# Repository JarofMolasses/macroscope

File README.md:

# Macroscope
This is a basic, constant-height, contact mode profilometer/AFM. It's really more of a demonstration piece but ~10 micron resolution can be achieved with some patience.

Inspired by this paper: [*Macro-scale atomic force microscope: An experimental platform for teaching precision mechatronics*](https://www.sciencedirect.com/science/article/abs/pii/S0957415815001488).

# Results
### Canadian nickel scanned at 1.75mm/s, 0.25mm resolution, 88x88 pixels 
A "quick" scan. It took 46 minutes.

### 3D printed test sample with 0.1mm steps. Scanned at 0.5mm/s, 0.05mm resolution, 60x20 pixels
You can see the diagonal print lines on the lowest step.

With a dollar for scale:

# Mechanical
## Initial working prototype 

## Second prototype 

# Control
This machine is programmed using SCPI-ish ASCII commands over a serial port.\
The control GUI we used for the prototype machines can be found here: https://github.com/JarofMolasses/macroscope_control. 

*Created by [David Antoniuk](https://github.com/DavidAntoniuk) and [myself](https://github.com/JarofMolasses).*

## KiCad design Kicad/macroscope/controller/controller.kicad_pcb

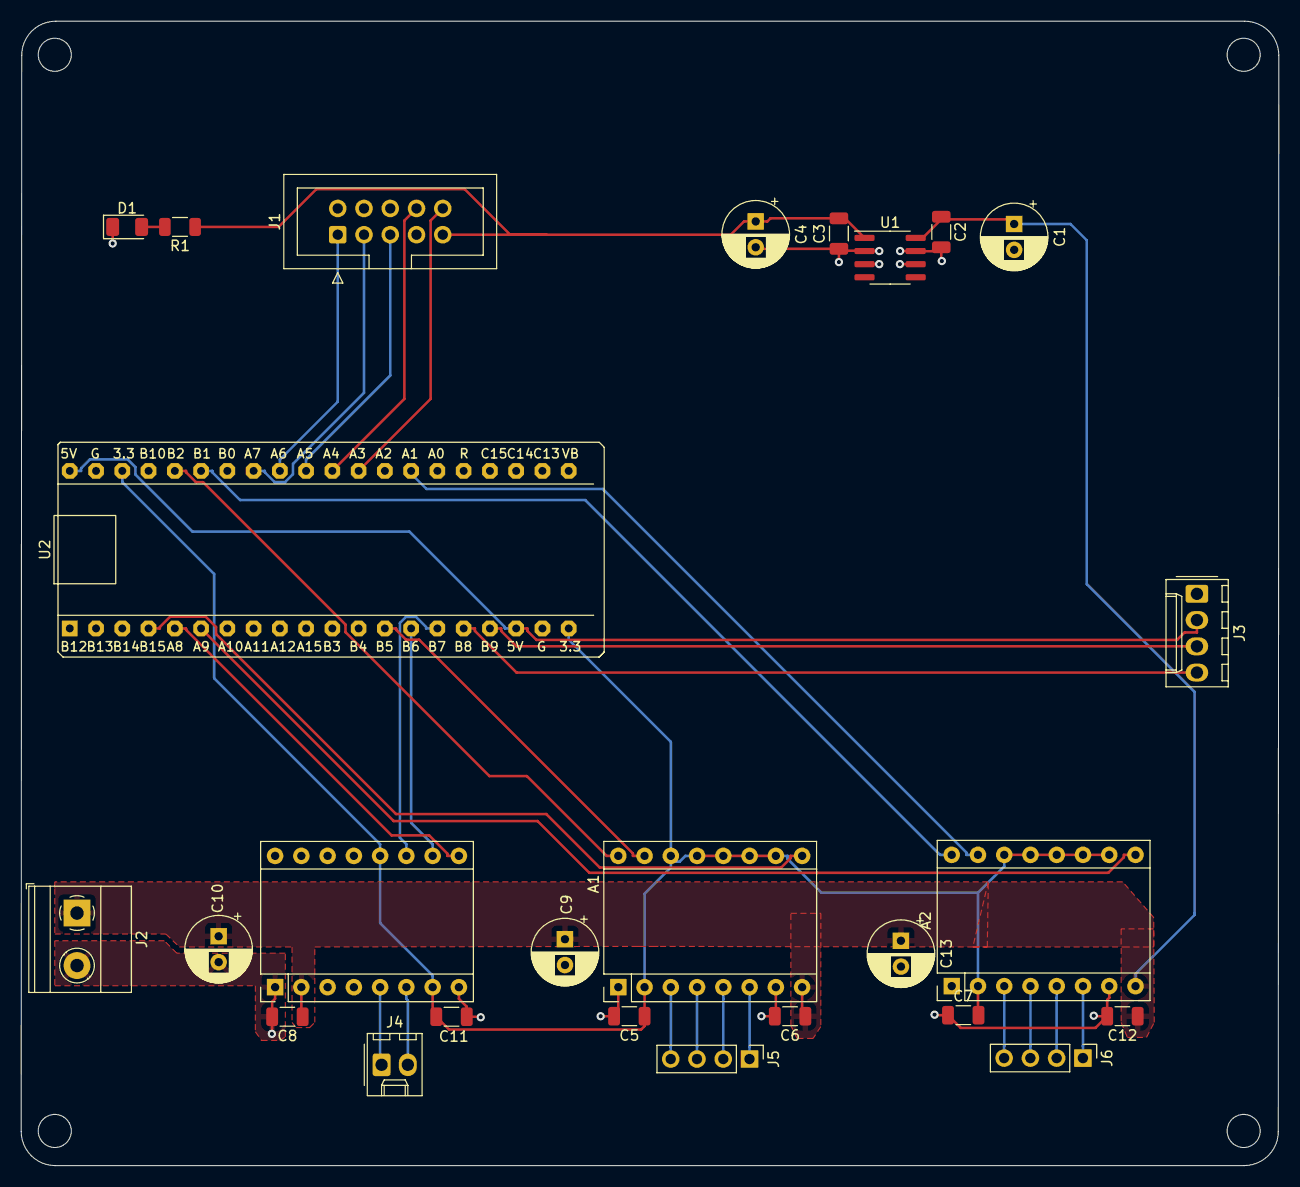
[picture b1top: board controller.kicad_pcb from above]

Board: 2 copper layers, 121.7 x 110.7 mm, 30 parts (0 on the bottom side), 32 nets.

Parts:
A1: A4988 Y axis driver; A4988_Pololu_Breakout-16_15.2x20.3mm
A2: A4988 X axis driver; A4988_Pololu_Breakout-16_15.2x20.3mm
C1, C4: 10u; CP_Radial_D6.3mm_P2.50mm
C2, C3, C6, C8, C12: 1u; C_1206_3216Metric
C5, C7, C11: 0.1u; C_1206_3216Metric
C9, C10, C13: 100u; CP_Radial_D6.3mm_P2.50mm
D1: LED; LED_1206_3216Metric
H1, H2, H3, H4: MountingHole; MountingHole_3.2mm_M3_ISO7380
J1: ADC board connector; IDC-Header_2x05_P2.54mm_Vertical
J2: 12V in; TerminalBlock_Phoenix_MKDS-1,5-2-5.08_1x02_P5.08mm_Horizont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
J3: I2C header; Molex_KK-254_AE-6410-04A_1x04_P2.54mm_Vertical
J4: Probe coil; Molex_KK-254_AE-6410-02A_1x02_P2.54mm_Vertical
J5: Y stepper; PinHeader_1x04_P2.54mm_Vertical
J6: X stepper; PinHeader_1x04_P2.54mm_Vertical
R1: 1k; R_1206_3216Metric
U1: LM78L05_SO8; SOIC-8_3.9x4.9mm_P1.27mm
U2: STM32F411 BlackPill; STM32F411_Black_Pill
U3: Coil driver; TB6612FNG_Pololu_Breakout-16_15.2x20.3mm

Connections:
+3V3: A1.2 (VDD), A1.10 (MS1), A1.11 (MS2), A1.12 (MS3), A1.13 (~RESET), A1.14 (~SLEEP), A2.2 (VDD), A2.10 (MS1), A2.11 (MS2), A2.12 (MS3), A2.13 (~RESET), A2.14 (~SLEEP), C5.1, C7.2, C11.1, U2.20 (3.3V), U2.38 (3.3V), U3.7 (VCC), U3.12 (STBY)
+5V: C3.1, C4.1, J1.9, R1.1, U1.1 (OUT)
+5VD: J3.2, U2.18 (5V), U2.40 (5V)
+12V: A1.8 (VMOT), A2.8 (VMOT), C1.1, C2.1, C6.1, C8.1, C9.1, C10.1, C12.1, C13.1, J2.1, U1.8 (IN), U3.2 (VMOT)
/Digital/COIL1: U2.14 (B6), U3.10 (AIN2)
/Digital/COIL2: U2.15 (B7), U3.11 (AIN1)
/Digital/DIRX: A1.16 (DIR), U2.36 (B2)
/Digital/DIRY: A2.16 (DIR), U2.35 (B1)
/Digital/ENX: A1.9 (~ENABLE), U2.4 (B15)
/Digital/ENY: A2.9 (~ENABLE), U2.6 (A9)
/Digital/PWM: U2.5 (A8), U3.9 (PWMA)
/Digital/SCL: J3.4, U2.16 (B8)
/Digital/SDA: J3.3, U2.17 (B9)
/Digital/STEPX: A1.15 (STEP), U2.13 (B5)
/Digital/STEPY: A2.15 (STEP), U2.27 (A1)
/Motion control/1Ax: A1.4 (1A), J5.3
/Motion control/1Ay: A2.4 (1A), J6.3
/Motion control/1Bx: A1.3 (1B), J5.4
/Motion control/1By: A2.3 (1B), J6.4
/Motion control/2Ax: A1.5 (2A), J5.2
/Motion control/2Ay: A2.5 (2A), J6.2
/Motion control/2Bx: A1.6 (2B), J5.1
/Motion control/2By: A2.6 (2B), J6.1
/Motion control/AO1: J4.2, U3.6 (AO1)
/Motion control/AO2: J4.1, U3.5 (AO2)
CS: J1.8, U2.30 (A4)
DRDY: J1.10, U2.29 (A3)
GND: A1.1 (GND), A1.7 (GND), A2.1 (GND), A2.7 (GND), C1.2, C2.2, C3.2, C4.2, C5.2, C6.2, C7.1, C8.2, C9.2, C10.2, C11.2, C12.2, C13.2, D1.1 (K), J1.7, J2.2, J3.1, U1.2 (GND), U1.3 (GND), U1.6 (GND), U1.7 (GND), U2.19 (G), U2.39 (G), U3.1 (GND), U3.8 (GND), U3.16 (GND)
MISO: J1.1, U2.32 (A6)
MOSI: J1.3, U2.33 (A7)
unnamed: D1.2 (A), R1.2
SCLK: J1.5, U2.31 (A5)

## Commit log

2023-12-02 Basic functionality with data stream confirmed
2023-12-09 Stable firmware
2023-12-14 Remove unecessary class
2023-12-17 Add kicad rough drafts
2023-12-18 Update Kicad files
2023-12-18 Slow down LCD default update rate
2025-08-22 Add CAD
